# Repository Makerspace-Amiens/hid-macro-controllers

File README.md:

# hid-macro-controllers
Projet pédagogique pour concevoir des périphériques HID (claviers macro, manettes, contrôleurs) en USB/BLE.

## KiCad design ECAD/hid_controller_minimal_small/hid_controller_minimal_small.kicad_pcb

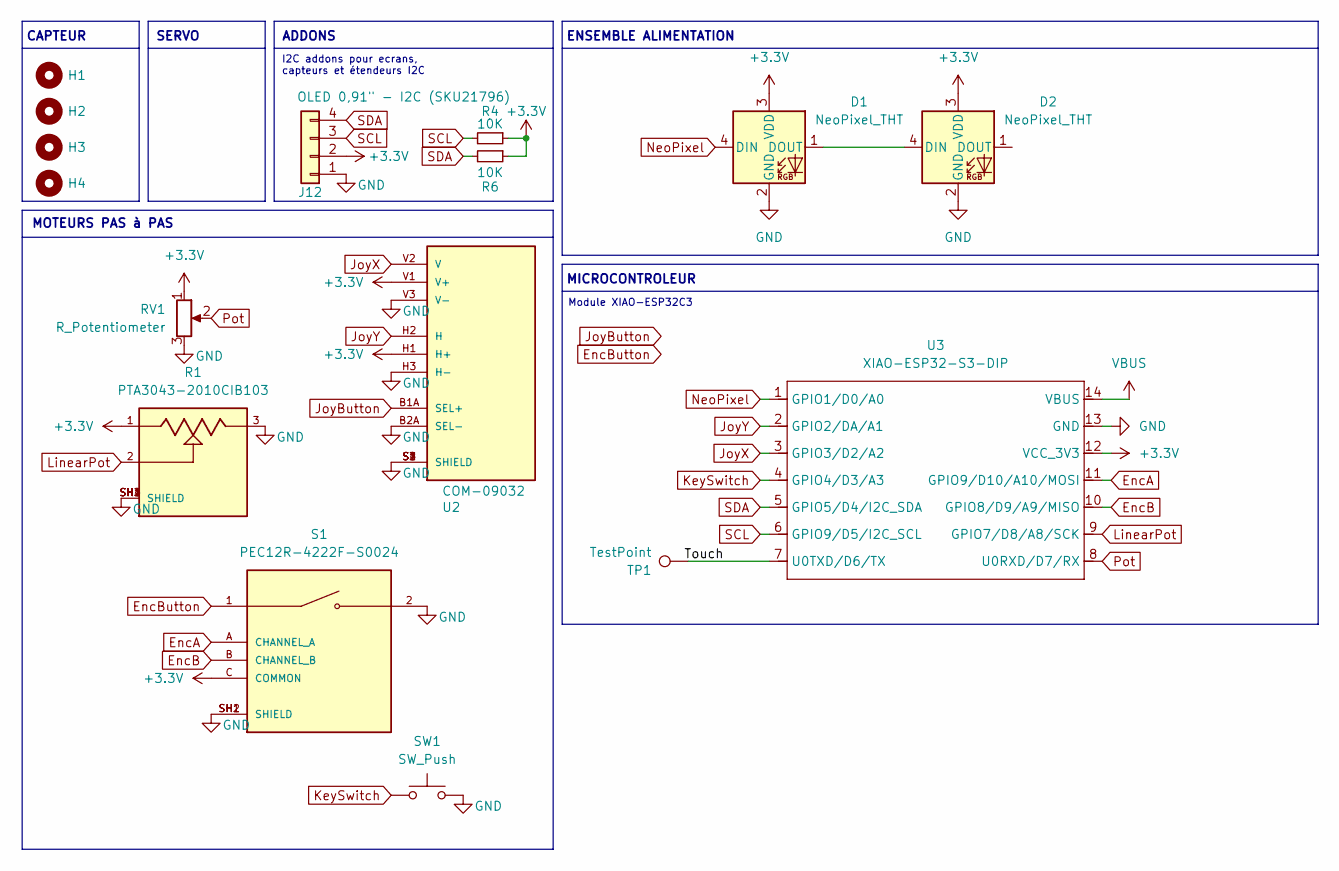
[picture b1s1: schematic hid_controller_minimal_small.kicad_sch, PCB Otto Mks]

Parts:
D1, D2: NeoPixel_THT; LED_D5.0mm-4_RGB
H1, H2, H3, H4: MountingHole; MountingHole_3.2mm_M3
J12: OLED 0,91" - I2C (SKU21796); PinSocket_1x04_P2.54mm_Vertical
R1: PTA3043-2010CIB103; TRIM_PTA3043-2010CIB103; PARTREV 04/21
R4, R6: 10K; R_Axial_DIN0204_L3.6mm_D1.6mm_P7.62mm_Horizontal
RV1: R_Potentiometer; Potentiometer_Bourns_PTV09A-1_Single_Vertical
S1: PEC12R-4222F-S0024; XDCR_PEC12R-4222F-S0024; PARTREV 07/21
SW1: SW_Push; SW_Cherry_MX_PCB_1.00u
TP1: TestPoint; TestPoint_Pad_D1.0mm
U2: COM-09032; XDCR_COM-09032; PARTREV N/A
U3: XIAO-ESP32-S3-DIP; XIAO-ESP32S3-DIP

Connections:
+3.3V: D1.3 (VDD), D2.3 (VDD), J12.2, R1.1, R4.1, R6.1, RV1.1, S1.C (COMMON), U2.H1 (H+), U2.V1 (V+), U3.12 (VCC_3V3)
/Touch: TP1.1, U3.7 (U0TXD/D6/TX)
EncA: S1.A (CHANNEL_A), U3.11 (GPIO9/D10/A10/MOSI)
EncB: S1.B (CHANNEL_B), U3.10 (GPIO8/D9/A9/MISO)
EncButton: S1.1
GND: D1.2 (GND), D2.2 (GND), J12.1, R1.3, R1.SH1 (SHIELD), R1.SH2 (SHIELD), R1.SH3 (SHIELD), R1.SH4 (SHIELD), RV1.3, S1.2, S1.SH1 (SHIELD), S1.SH2 (SHIELD), SW1.2, U2.B2A (SEL-), U2.H3 (H-), U2.S1 (SHIELD), U2.S2 (SHIELD), U2.S3 (SHIELD), U2.S4 (SHIELD), U2.V3 (V-), U3.13 (GND)
JoyButton: U2.B1A (SEL+)
JoyX: U2.V2 (V), U3.3 (GPIO3/D2/A2)
JoyY: U2.H2 (H), U3.2 (GPIO2/DA/A1)
KeySwitch: SW1.1, U3.4 (GPIO4/D3/A3)
LinearPot: R1.2, U3.9 (GPIO7/D8/A8/SCK)
NeoPixel: D1.4 (DIN), U3.1 (GPIO1/D0/A0)
unnamed: D1.1 (DOUT), D2.4 (DIN)
Pot: RV1.2, U3.8 (U0RXD/D7/RX)
SCL: J12.3, R4.2, U3.6 (GPIO9/D5/I2C_SCL)
SDA: J12.4, R6.2, U3.5 (GPIO5/D4/I2C_SDA)
VBUS: U3.14 (VBUS)

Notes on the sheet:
CAPTEUR
MOTEURS PAS à PAS
ADDONS
ENSEMBLE ALIMENTATION
SERVO
Module XIAO-ESP32C3
I2C addons pour ecrans, capteurs et étendeurs I2C
MICROCONTROLEUR

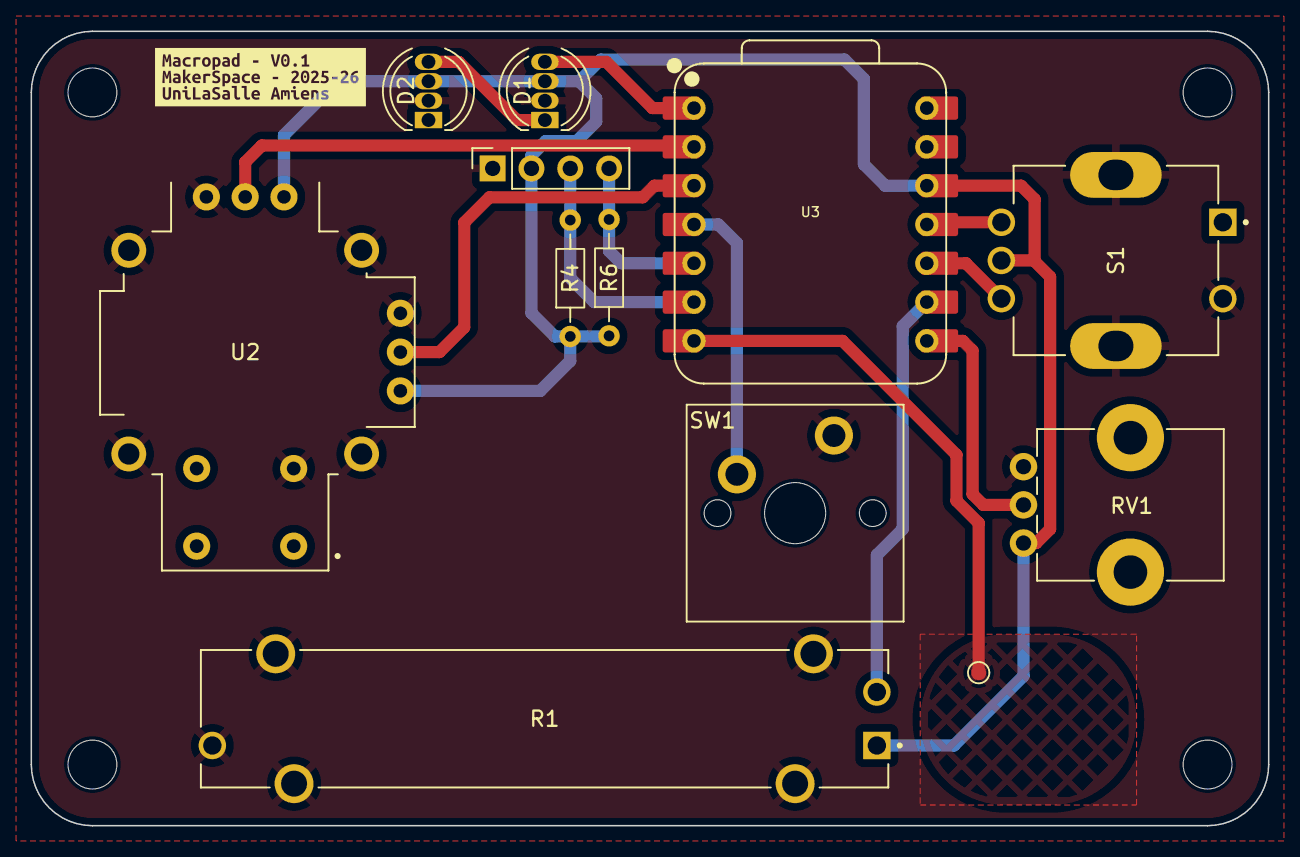
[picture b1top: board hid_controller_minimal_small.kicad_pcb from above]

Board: 2 copper layers, 81.0 x 52.0 mm, 17 parts (0 on the bottom side), 14 nets.

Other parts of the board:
kibuzzard-68AC773C: G***; kibuzzard-68AC773C

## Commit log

2025-08-22 pcb test
2025-08-25 Small version for testing IO
